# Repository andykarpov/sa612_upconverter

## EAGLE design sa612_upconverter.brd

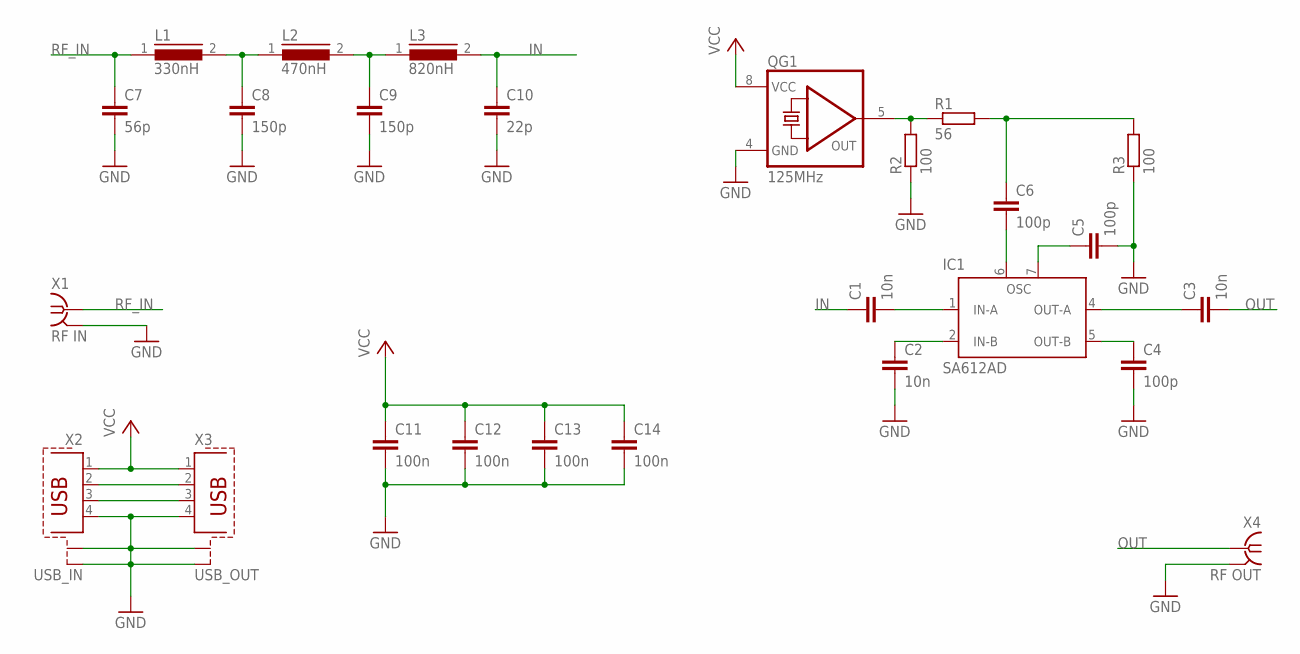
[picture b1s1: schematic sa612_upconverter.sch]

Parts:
C1, C2, C3: 10n; C2.5-2
C4, C6: 100p; C2.5-2
C5: 100p; C7.5B3
C7: 56p; C2.5-2
C8, C9: 150p; C2.5-2
C10: 22p; C2.5-2
C11, C12, C13, C14: 100n; C2.5-2
IC1: SA612AD; SO08
L1: 330nH; ED16
L2: 470nH; ED16
L3: 820nH; ED16
QG1: 125MHz; DIL08S
R1: 56; 0204/7
R2, R3: 100; 0204/7
X1: RF IN; BU-SMA-H
X2: USB_IN; PN61729-S
X3: USB_OUT; PN87520-S
X4: RF OUT; BU-SMA-V

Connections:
GND: C2.2, C4.2, C5.2, C7.2, C8.2, C9.2, C10.2, C11.2, C12.2, C13.2, C14.2, IC1.3 (GND), QG1.4 (GND), R2.1, R3.1, X1.2, X1.3 (2), X1.4 (2), X1.5 (2), X2.4, X2.S1, X2.S2, X3.4, X3.S1, X3.S2, X4.2, X4.3 (2), X4.4 (2), X4.5 (2)
IN: C1.1, C10.1, L3.2
unnamed: QG1.5 (OUT), R1.1, R2.2
unnamed: C4.1, IC1.5 (OUT-B)
unnamed: C3.1, IC1.4 (OUT-A)
unnamed: C1.2, IC1.1 (IN-A)
unnamed: C2.1, IC1.2 (IN-B)
unnamed: C5.1, IC1.7 (OSC')
unnamed: C6.1, R1.2, R3.2
unnamed: C6.2, IC1.6 (OSC)
unnamed: C8.1, L1.2, L2.1
unnamed: C9.1, L2.2, L3.1
unnamed: X2.2, X3.2
unnamed: X2.3, X3.3
OUT: C3.2, X4.1
RF_IN: C7.1, L1.1, X1.1
VCC: C11.1, C12.1, C13.1, C14.1, IC1.8 (VCC), QG1.8 (VCC), X2.1, X3.1

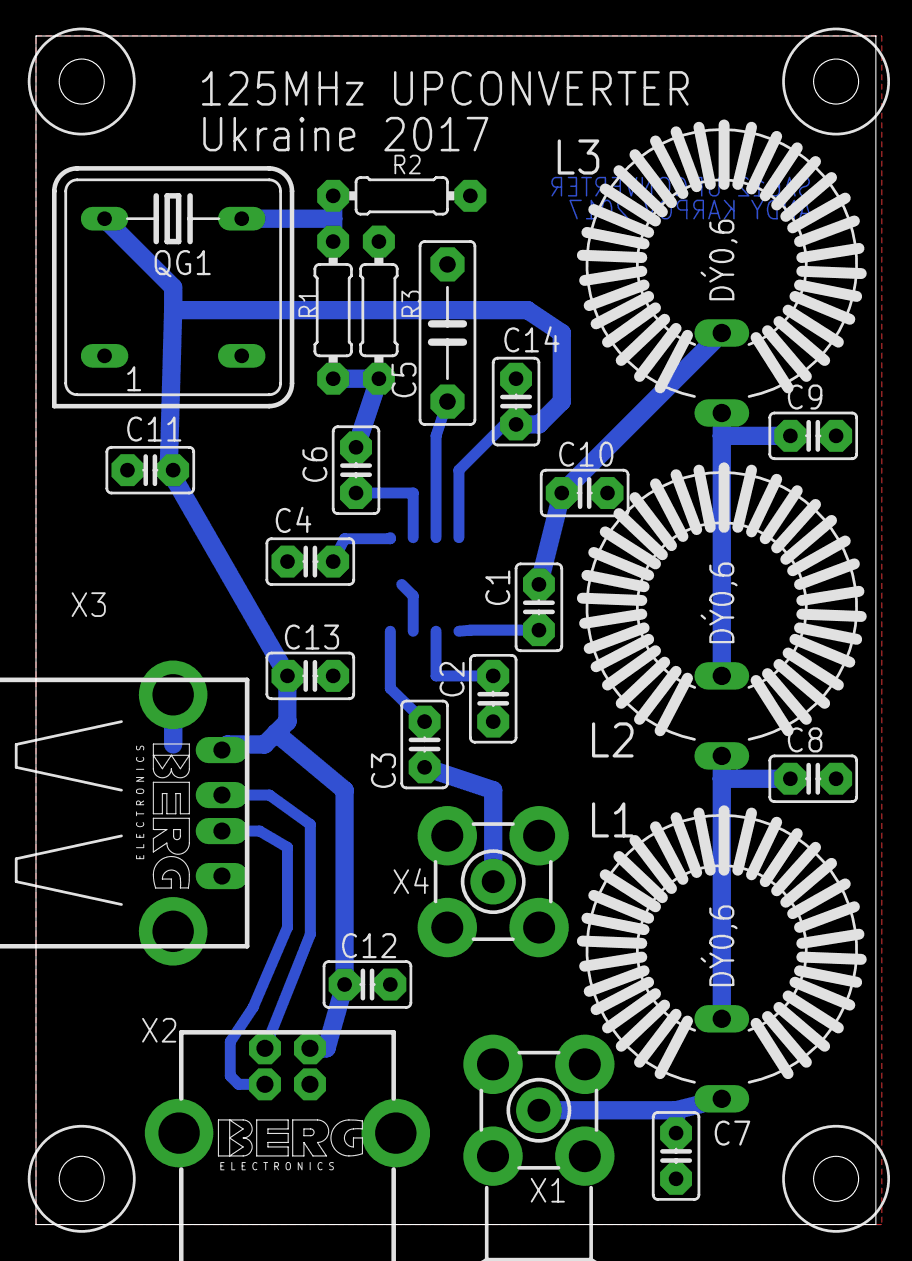
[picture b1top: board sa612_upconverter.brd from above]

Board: 2 copper layers, 46.7 x 66.0 mm, 30 parts (1 on the bottom side), 17 nets.

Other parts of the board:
U$1, U$2, U$3, U$4: DRIL-2,5

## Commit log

2017-04-09 docs
